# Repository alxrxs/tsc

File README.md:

---
# InkTime -- Smartwatch Open Source cu Display E-Paper
**TSC 2026 -- Andrei-Alexandru Bleortu, 334CA**

---

## Descriere proiect

InkTime este un smartwatch open source cu display e-paper, construit in jurul SoC-ului Nordic nRF52840. Schema electrica a fost furnizata de profesor; sarcina mea a fost sa o transpun in Fusion 360, sa realizez layout-ul PCB si sa-l integrez in carcasa data.

PCB-ul are dimensiunile 36x38mm, grosime 1mm, 4 straturi (TOP, GND, POWER, BOTTOM), cu toate componentele pe layer-ul TOP.

---

## Diagrama bloc

```
                          +--------------------------------------------+
                          |              nRF52840 (U1)                 |
                          |                                            |
  +--------------+  VBUS  |  USB/VBUS                                  |
  |  USB-C (J4)  |------->|                      P0.02 (SCK)  ---------+------------------+
  | KH-TYPE-C-16P|  D+/D- |  USB D+/D-           P0.03 (MOSI) ---------+--------------+   |
  +------+-------+<------>|                      P0.05 (CS)   ---------+----------+   |   |
         |                |  P0.06 (SDA)  ---------------------------- +--+       |   |   |
  +------v-------+        |  P0.07 (SCL)  ---------------------------- +--+ I2C   |   |   |
  |  USBLC6-2SC6Y|        |                      P0.15 (EPD_DC)  ------+--+       |   |SPI|
  |  ESD (D3)    |        |  P0.08 (IMU_INT1)                   P0.16 -+--+       |   |   |
  +------+-------+        |  P1.08 (IMU_INT2)                   P0.17 -+--+       |   |   |
         |                |  P0.11 (PMIC_INT)                          |          |   |   |
  +------v-------+  VREG  |  P0.10 (ALERT)        P1.01 (EPD PWR EN)-->|          |   |   |
  |  BQ25180YBGR |------->|  P0.12 (HAPTIC_EN)                         |          |   |   |
  |  Incarcator  |        |                                            |          |   |   |
  +------+-------+        |  P0.13 (SW1)                               |          |   |   |
         | VBAT           |  P0.14 (SW2)                               |          |   |   |
  +------v-------+        |  P1.02 (SW3)                               |          |   |   |
  |  Baterie     |        |              SWDIO/SWDCLK/SWO/RESET        |          |   |   |
  |  Li-Po       |        |  P0.00/P0.01 (XL1/XL2) <-- X2 32.768kHz    |          |   |   |
  +------+-------+        |  XC1/XC2  <--------------- X1 32MHz        |          |   |   |
         |                |                      ANT  --> Retea RF     |          |   |   |
  +------v-------+        +--------------------------------------------+          |   |   |
  | MAX17048G+T10|<------------------------------- I2C ---------------------------+   |   |
  | Fuel Gauge   |                                                                    |   |
  +--------------+        Magistrala I2C (SDA=P0.06, SCL=P0.07):                      |   |
                          +--------------+  +--------------+  +--------------+        |   |
                          | RT6160AWSC   |  |  BMA421 (IC3)|  | DRV2605YZFR  |        |   |
                          | Buck-Boost   |  |  IMU/Accel.  |  | Haptic (IC2) |        |   |
                          | -> 3V3 (IC9) |  |              |  | -> Motor     |        |   |
                          +--------------+  +--------------+  +--------------+        |   |
                                                                                      |   |
                          Magistrala SPI (SCK=P0.02, MOSI=P0.03):                     |   |
                          +-----------------------------------------------------------+   |
                          |  503480-2400 FPC (J2) -> Display E-Paper                      |
                          |  CS=P0.05, DC=P0.15, RST=P0.16, BUSY=P0.17  <-----------------+
                          +----------------------------------------------

                          Butoane: SW1(P0.13) SW2(P0.14) SW3(P1.02)
                          Debug:   TC2030-IDC (J1) -> SWD + RESET
                          Antena:  2450AT18B100E + retea de adaptare L-C
```

---

## Bill of Materials (BOM)

| Ref | Componenta | Valoare / MPN | Capsula | Cant | JLCPCB | Datasheet |
|-----|------------|---------------|---------|------|--------|-----------|
| U1 | MCU nRF52840 | NRF52840-QIAA-R | AQFN-74 (7x7mm) | 1 | [C190794](https://jlcpcb.com/partdetail/NordicSemiconductor-nRF52840QIAA/C190794) | [Datasheet](https://infocenter.nordicsemi.com/pdf/nRF52840_PS_v1.7.pdf) |
| IC1 | Incarcator baterie | BQ25180YBGR | DSBGA-8 (1.6x1.1mm) | 1 | [C3682423](https://jlcpcb.com/partdetail/C3682423) | [Datasheet](https://www.ti.com/lit/ds/symlink/bq25180.pdf) |
| IC9 | Regulator Buck-Boost DC-DC | RT6160AWSC | WLCSP-15 (2.3x1.4mm) | 1 | [C7065276](https://jlcpcb.com/partdetail/C7065276) | [Datasheet](https://www.richtek.com/assets/product_file/RT6160A/DS6160A-00.pdf) |
| IC3 | IMU / Accelerometru | BMA421 | LGA-12 (2x2mm) | 1 | [C5242966](https://jlcpcb.com/partdetail/BoschSensortec-BMA421/C5242966) | [Datasheet](https://files.pine64.org/doc/datasheet/pinetime/BST-BMA421-FL000.pdf) |
| IC2 | Driver motor haptic | DRV2605YZFR | DSBGA-9 | 1 | [C81079](https://jlcpcb.com/partdetail/C81079) | [Datasheet](https://www.ti.com/lit/ds/symlink/drv2605.pdf) |
| U2 | Fuel gauge Li-Po | MAX17048G+T10 | WLP-8 (0.9x1.8mm) | 1 | [C2682616](https://jlcpcb.com/partdetail/C2682616) | [Datasheet](https://www.analog.com/media/en/technical-documentation/data-sheets/max17048-max17049.pdf) |
| J4 | Conector USB-C | KH-TYPE-C-16P | SMD 16P | 1 | [C709357](https://jlcpcb.com/partdetail/C709357) | [Datasheet](https://datasheet.lcsc.com/lcsc/2108252330_Korean-Hroparts-Elec-TYPE-C-31-M-12_C165948.pdf) |
| J2 | Conector FPC (e-Paper) | 503480-2400 | SMD 24P, pas 0.5mm | 1 | [C122434](https://jlcpcb.com/partdetail/C122434) | [Datasheet](https://www.molex.com/content/dam/molex/molex-dot-com/products/automated/en-us/salesdrawingpdf/503/5034/503480-2400_sd.pdf) |
| J1 | Conector debug | TC2030-IDC | Tag-Connect 6P | 1 | N/A (footprint) | [Datasheet](https://www.tag-connect.com/wp-content/uploads/bsk-pdf-manager/TC2030-IDC-NL_Datasheet_8.pdf) |
| ANT1 | Antena chip 2.4GHz | 2450AT18B100E | SMD 1.6x0.8mm | 1 | [C2917717](https://jlcpcb.com/partdetail/C2917717) | [Datasheet](https://www.johansontechnology.com/datasheets/2450AT18B100E/2450AT18B100E.pdf) |
| D3 | Protectie ESD USB | USBLC6-2SC6Y | SOT-363 | 1 | [C2969755](https://jlcpcb.com/partdetail/C2969755) | [Datasheet](https://www.st.com/resource/en/datasheet/usblc6-2.pdf) |
| D2, D4, D5 | Dioda Schottky | MBR0530 | SOD-123 | 3 | [C232832](https://jlcpcb.com/partdetail/C232832) | [Datasheet](https://www.onsemi.com/pdf/datasheet/mbr0530t1-d.pdf) |
| Q1 | N-MOSFET (driver EPD) | SI1308EDL-T1-GE3 | SC-70-3 | 1 | [C469327](https://jlcpcb.com/partdetail/C469327) | [Datasheet](https://www.vishay.com/docs/66783/si1308edl.pdf) |
| Q2 | P-MOSFET (alimentare EPD) | DMG2305UX-7 | SOT-323 | 1 | [C150470](https://jlcpcb.com/partdetail/C150470) | [Datasheet](https://www.diodes.com/assets/Datasheets/DMG2305UX.pdf) |
| SW1, SW2, SW3 | Buton tactil | EVP-AKE31A | SMD | 3 | [C569760](https://jlcpcb.com/partdetail/C569760) | [Datasheet](https://industrial.panasonic.com/cdbs/www-data/pdf/ATV0000/ATV0000CE15.pdf) |
| X1 | Crystal HF | 32MHz | SMD 3225 | 1 | [C113671](https://jlcpcb.com/partdetail/C113671) | -- |
| X2 | Crystal LF (RTC) | 32.768kHz | SMD | 1 | [C145140](https://jlcpcb.com/partdetail/C145140) | -- |
| L7 | Inductor (DC-DC) | FTC252012SR47MBCA / 0.47uH | 0402 | 1 | [C5832368](https://jlcpcb.com/partdetail/C5832368) | [Datasheet](https://product.tdk.com/system/files/dam/doc/product/inductor/inductor/smd/catalog/inductor_commercial_power_mlp2016_en.pdf) |
| L1 | Inductor adaptare antena | 3.9nH | 0402 | 1 | -- | -- |
| L2 | Inductor decuplare RF | 10uH | 0402 | 1 | -- | -- |
| L3 | Inductor decuplare RF | 15nH | 0402 | 1 | -- | -- |
| L5 | Inductor (boost EPD) | 68uH | 0402 | 1 | -- | -- |
| C1, C2 | Condensator sarcina crystal HF | 12pF | 0201 | 2 | [C426109](https://jlcpcb.com/partdetail/C426109) | -- |
| C17, C18 | Condensator sarcina crystal LF | 12pF | 0201 | 2 | [C426109](https://jlcpcb.com/partdetail/C426109) | -- |
| C3, C4 | Condensator adaptare antena | 1pF | 0201 | 2 | [C185624](https://jlcpcb.com/partdetail/C185624) | -- |
| C8, C12, C7, C5 | Condensator decuplare | 100nF | 0201 | 4 | [C160831](https://jlcpcb.com/partdetail/C160831) | -- |
| C6, C14, C20, C21 | Condensator bulk | 4.7uF | 0402 | 4 | [C23687](https://jlcpcb.com/partdetail/C23687) | -- |
| C24, C39 | Condensator bulk (VREG) | 10uF | 0402 | 2 | [C105884](https://jlcpcb.com/partdetail/C105884) | -- |
| C25, C33 | Condensator iesire (3V3) | 22uF | 0402 | 2 | [C919306](https://jlcpcb.com/partdetail/C919306) | -- |
| C37, C38 | Condensator filtru PMIC | 1uF | 0402 | 2 | [C268023](https://jlcpcb.com/partdetail/C268023) | -- |
| R17, R18 | Rezistenta pull-up I2C | 3.3kohm | 0201 | 2 | [C274874](https://jlcpcb.com/partdetail/C274874) | -- |
| R5, R7, R8 | Rezistenta pull-up butoane | 10kohm | 0201 | 3 | [C106225](https://jlcpcb.com/partdetail/C106225) | -- |
| R9, R2_EP_DR, R_PWR_EPD | Pull-up / configurare | 10kohm | 0201 | 3 | [C106225](https://jlcpcb.com/partdetail/C106225) | -- |
| R1_USB, R2_USB | Rezistente CC USB-C | 5.1kohm | 0201 | 2 | [C274341](https://jlcpcb.com/partdetail/C274341) | -- |
| R1, R2, R4 | Jumper zero-ohm | 0ohm | 0201 | 3 | [C106227](https://jlcpcb.com/partdetail/C106227) | -- |
| R1_EP_DR | Rezistenta limitare curent EPD | 0.47ohm | 0201 | 1 | -- | -- |
| R_TYPE_SEL | Selectie tip display | 2.2ohm | 0201 | 1 | -- | -- |
| EPD_C1-C12 | Condensatoare HV EPD | 1uF/50V | 0402 | 9 | -- | -- |
| C29-C32 | Condensator debounce butoane | 1uF | 0402 | 4 | [C268023](https://jlcpcb.com/partdetail/C268023) | -- |

---

## Descriere hardware

### Componentele principale

**nRF52840 (U1)** -- MCU central. Cortex-M4F la 64MHz, 1MB flash, 256KB RAM, radio 2.4GHz integrat (BLE 5.0 + IEEE 802.15.4). Capsula AQFN-74, 7x7mm, 74 de pad-uri.

**BQ25180YBGR (IC1)** -- incarcator Li-Po single-cell de la Texas Instruments. Gestioneaza power path-ul USB-C, curentul de incarcare configurabil prin I2C (pana la 350mA), si semnalizeaza evenimentele de stare prin pinul INT (PMIC_INT -> P0.11). Adresa I2C: 0x6A.

**RT6160AWSC (IC9)** -- regulator buck-boost de la Richtek, WLCSP-15. Converteste tensiunea variabila a bateriei (3.0-4.2V) in 3.3V stabil pentru restul circuitului. Controlabil prin I2C. Adresa I2C: 0x75 (7-bit, conform datasheet sectiunea 16.23).

**BMA423 (IC3)** -- accelerometru triaxial Bosch, LGA-12 (2x2mm). Are numarator de pasi si detectie de gesturi integrate in hardware. Comunica prin I2C, adresa 0x18 (pinul CSB legat la 3V3, SDO legat la GND prin R1). Doua linii de intrerupere: INT1 -> P0.08, INT2 -> P1.08.

**DRV2605YZFR (IC2)** -- driver motor haptic de la Texas Instruments, DSBGA-9. Controleaza un motor ERM sau LRA, cu biblioteca de tipare de vibratie integrata. I2C, adresa 0x5A. Activat prin HAPTIC_EN (P0.12).

**MAX17048G+T10 (U2)** -- fuel gauge Li-Po de la Maxim/ADI, WLP-8. Estimeaza starea de incarcare a bateriei prin algoritmul ModelGauge (fara rezistenta de sunt). I2C, adresa 0x36. Semnalul !ALERT merge la P0.10.

---

### Arhitectura de alimentare

```
USB-C (5V VBUS)
     |
     v
BQ25180 (IC1) -- incarcare baterie + power path
     | SYS -> sina VREG
     v
RT6160 (IC9) -- buck-boost
     | VOUT = 3.3V -> sina 3V3
     v
nRF52840, BMA423, DRV2605, MAX17048
```

Alimentarea display-ului e-paper este separata: Q2 (P-MOSFET DMG2305UX-7) comuteaza sina EPD_3V3, controlat de P1.01. Tensiunile de gate driver (PREVGH/PREVGL, +/-20V) sunt generate de un circuit boost cu L5 (68uH), Q1 (N-MOSFET SI1308EDL) si trei diode Schottky MBR0530.

---

### Pini nRF52840 utilizati

| GPIO | Functie | Conectat la |
|------|---------|-------------|
| P0.00 / XL1 | Crystal LF XL1 | X2 (32.768kHz) |
| P0.01 / XL2 | Crystal LF XL2 | X2 (32.768kHz) |
| P0.02 | SPI SCK | J2 pin 13 (display) |
| P0.03 | SPI MOSI | J2 pin 14 (display) |
| P0.05 | EPD CS | J2 pin 12 |
| P0.06 | I2C SDA | IC1, IC9, IC3, U2, IC2 |
| P0.07 | I2C SCL | IC1, IC9, IC3, U2, IC2 |
| P0.08 | IMU INT1 | IC3 (BMA423) |
| P0.10 / NFC2 | ALERT (fuel gauge) | U2 (MAX17048) |
| P0.11 | PMIC_INT | IC1 (BQ25180) |
| P0.12 | HAPTIC_EN | IC2 (DRV2605) |
| P0.13 | SW1 | Buton + pull-up 10kohm |
| P0.14 | SW2 | Buton + pull-up 10kohm |
| P0.15 | EPD DC | J2 pin 11 |
| P0.16 | EPD RST | J2 pin 10 |
| P0.17 | EPD BUSY | J2 pin 9 |
| P0.18 / RESET | RESET | TC2030 J1, TP_RESET |
| P1.00 | SWO | TC2030 J1, TP_SWO |
| P1.01 | EPD power enable | Gate Q2 |
| P1.02 | SW3 | Buton + pull-up 10kohm |
| P1.08 | IMU INT2 | IC3 (BMA423) |
| SWDIO | SWD Data | TC2030 J1, TP_SWDIO |
| SWDCLK | SWD Clock | TC2030 J1, TP_SWDCLK |
| VBUS | Detectare VBUS | BQ25180 IN + J4 |
| D+ / D- | USB Full-Speed | USBLC6-2SC6Y (D3) |
| XC1, XC2 | Crystal HF | X1 (32MHz) |

Pinii P0.04, P0.09, P0.19-P0.31, P1.03-P1.07, P1.09-P1.15 nu sunt utilizati in schema.

---

### Interfete de comunicatie

**I2C** (SDA=P0.06, SCL=P0.07) -- magistrala partajata cu 5 dispozitive:
- BQ25180 (0x6A) -- incarcator
- RT6160 (0x75) -- regulator DC-DC
- BMA423 (0x18) -- IMU
- MAX17048 (0x36) -- fuel gauge
- DRV2605 (0x5A) -- driver haptic

Pull-up-uri de 3.3kohm (R17, R18) pe ambele linii. R4 si R2 sunt rezistente de 0ohm care conecteaza IC9 (RT6160) la magistrala -- pot fi inlaturate pentru izolare la nevoie.

**SPI** (SCK=P0.02, MOSI=P0.03, CS=P0.05) -- exclusiv pentru display-ul e-paper prin conectorul FPC J2 (Molex 503480-2400, 24 pini, pas 0.5mm). Semnale suplimentare: DC (P0.15), RST (P0.16), BUSY (P0.17).

**USB Full-Speed** -- D+/D- merg prin USBLC6-2SC6Y (D3) pentru protectie ESD, apoi la pinii dedicati ai nRF52840. Rezistentele CC de 5.1kohm (R1_USB, R2_USB) identifica dispozitivul ca UFP pe USB-C.

**SWD** -- SWDIO, SWDCLK, SWO (P1.00), RESET (P0.18) disponibili prin conectorul Tag-Connect TC2030-IDC (J1) si pad-urile de test corespunzatoare.

---

### Ceas si RF

**Cristale:** X1 (32MHz) pe pinii XC1/XC2 -- necesar pentru radio BLE. X2 (32.768kHz) pe P0.00/P0.01 (XL1/XL2) -- pentru RTC. Condensatori de sarcina de 12pF pe ambele cristale.

**Antena:** 2450AT18B100E (Johanson Technology), chip antenna SMD 1.6x0.8mm. Conectata prin retea de adaptare Pi: L1 (3.9nH) serie si C3/C4 (1pF) shunt. C22 montat N.C. (rezervat pentru acordaj). Antena este plasata la marginea PCB-ului, cu decupaj in placa sub ea -- fara cupru si fara trasee in acea zona.

---

### Butoane

Trei butoane tactile Panasonic EVP-AKE31A, active-low, cu pull-up de 10kohm la 3V3 si condensator de debounce de 1uF pe fiecare linie.

| Buton | GPIO | Pull-up | Debounce |
|-------|------|---------|----------|
| SW1 | P0.13 | R5 | C30 |
| SW2 | P0.14 | R8 | C31 |
| SW3 | P1.02 | R7 | C29 |

---

### Debug

TC2030-IDC (J1) -- footprint Tag-Connect, fara conector fizic pe placa. Pinout:

| Pin | Semnal |
|-----|--------|
| 1 | 3V3 |
| 2 | SWDIO |
| 3 | GND |
| 4 | SWDCLK |
| 5 | GND |
| 6 | RESET |

Pad-uri de test disponibile in silkscreen: TP_SWDIO, TP_SWDCLK, TP_SWO, TP_RESET, TP_3.3V, TP_GND, TP_VBAT, TP_BAT_GND, TP_3V3, TP_VREG, TP_SCL, TP_SDA, TP_OP, TP_ON.

---

## Estimari consum

Calcule estimative bazate pe datasheeturile componentelor.

| Mod | Contribuitori | Curent estimat |
|-----|---------------|----------------|
| Deep sleep (doar RTC) | nRF52840 system-on: ~2.6uA, BMA423 low-power: ~3.5uA, MAX17048: ~3uA, RT6160 quiescent: ~60uA, DRV2605 standby: ~40uA | **~110uA** |
| BLE advertising (1s interval) | nRF52840 medie advertising: ~0.5mA + ~110uA sistem | **~0.6mA** |
| Activ (BLE conectat + refresh display) | nRF52840: ~4mA, varf refresh: ~26mA (cateva secunde), IMU: ~150uA | **~5-30mA** |
| Incarcare USB | BQ25180 la 200mA | **~200mA** |

Cu o baterie de 400mAh si un tipar de utilizare de ~5 minute activ + 55 minute standby pe ora, curentul mediu iese in jur de 0.5-0.6mA, ceea ce teoretic da cateva saptamani de autonomie. In practica, cu stack-ul BLE si refresh-uri regulate de display, realitatea va fi probabil undeva la 5-7 zile.

---

## Note PCB

Schema electrica a fost furnizata de dl. Tudose. Munca mea a constat in transpunerea ei in Fusion 360 si realizarea layout-ului PCB conform specificatiilor primite.

**Constrangeri respectate:**
- PCB 4 straturi: TOP (componente + rutare), GND (plan de masa dedicat), POWER (plan de alimentare), BOTTOM (rutare)
- Toate componentele plasate pe layer-ul TOP
- Trasee de putere (3V3, VBUS, VREG) cu latime 0.3mm; semnale de date minimum 0.15mm
- Condensatoarele de decuplare de 100nF plasate cat mai aproape de pinii de alimentare ai IC-urilor
- Fara cupru si fara trasee sub antena; decupaj PCB inclus sub 2450AT18B100E
- Fara unghiuri de 90deg in trasee

**Observatie privind BMA421 vs BMA423:** in schema deviceset-ul este BMA423, dar valoarea componentei scrie BMA421. Cele doua sunt pin-compatibile (acelasi footprint LGA-12, 2x2mm), deci nu afecteaza PCB-ul.

---

## Structura repository-ului

```
+-- Hardware/
|   +-- Schematic.sch          -- Schema electrica (Fusion 360 / Eagle)
|   +-- Board.brd              -- Layout PCB (Fusion 360 / Eagle)
|   +-- Schematic.pdf          -- Printout schema
+-- Manufacturing/
|   +-- gerbers.zip            -- Fisiere Gerber pentru fabricare
|   +-- InkTime.bom            -- Bill of Materials (CSV)
|   +-- InkTime.cpl            -- Pick and Place (CSV)
+-- Mechanical/
|   +-- InkTime_complete.step  -- Vedere 3D explodata (STEP)
|   +-- InkTime_complete.f3d   -- Asamblare Fusion 360
+-- Images/
|   +-- *.png                  -- Randari PCB si 3D
+-- LICENSE                    -- Apache 2.0
+-- README.md                  -- Acest fisier
```

---

## Licenta

GNU Affero General Public License. Vezi [LICENSE](LICENSE).

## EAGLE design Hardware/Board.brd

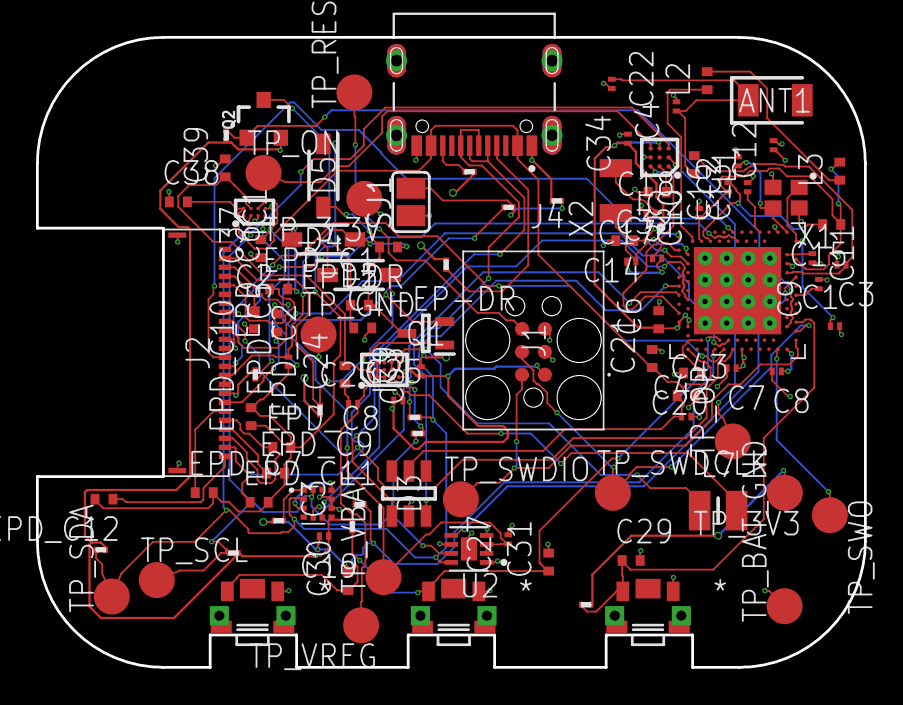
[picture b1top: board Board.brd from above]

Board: 4 copper layers, 46.0 x 35.0 mm, 105 parts (0 on the bottom side), 73 nets.

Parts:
ANT1: 2450AT18B100E; 2450AT18B100E_ANTC3216X140N
C1, C2, C17, C18: 12pF; NORDIC_NRF_3_RESC0201_L
C1-EP-DR, C24, C39: 10uF; NORDIC_NRF_3_RESC0402_L
C2-EP-DR: 4.7uF/25V; NORDIC_NRF_3_RESC0402_L
C3, C4: 1pF; NORDIC_NRF_3_RESC0201_L
C5, C7, C8, C12, C19: 100nF; NORDIC_NRF_3_RESC0201_L
C6, C14, C20, C21, C43: 4.7uF; NORDIC_NRF_3_RESC0402_L
C9: 820pF; NORDIC_NRF_3_RESC0201_L
C10, C13, C22: N.C.; NORDIC_NRF_3_RESC0201_L
C11: 100pF; NORDIC_NRF_3_RESC0201_L
C15: 1.0uF; NORDIC_NRF_3_RESC0402_L
C16: 47nF; NORDIC_NRF_3_RESC0201_L
C23, C27, C34, C42: 0.1uF; NORDIC_NRF_3_RESC0201_L
C25, C33: 22uF; NORDIC_NRF_3_RESC0201_L
C29, C30, C31, C32, C37, C38: 1uF; NORDIC_NRF_3_RESC0402_L
D2, D4, D5: MBR0530; ESP32_C6_LIBRARY_5_SOD3716X135N
D3: USBLC6-2SC6Y; ESP32_C6_LIBRARY_3_SOT95P280X145-6N
EPD_C1, EPD_C2, EPD_C6, EPD_C7, EPD_C8, EPD_C9, EPD_C10, EPD_C11, EPD_C12: 1uF/50V; NORDIC_NRF_3_RESC0402_L
EPD_C5: 0.1uF/50V; NORDIC_NRF_3_RESC0201_L
IC1: BQ25180YBGR; BQ25180YBGR_BGA8C40P2X4_100X155X50
IC2: DRV2605YZFR; DRV2605YZFR_BGA9C50P3X3_144X144X62
IC3: BMA421; BMA423_BMA423
IC9: RT6160AWSC; RT6160AWSC_BGA15C40P3X5_140X230X60
J1: TC2030-IDC; TC2030-IDC_TC2030IDC
J2: 503480-2400; 503480-2400_5034802400
J4: KH-TYPE-C-16P; KH-TYPE-C-16P_KINGHELM_KH-TYPE-C-16P
L1: 3.9nH; NORDIC_NRF_2_RESC0402_L
L2: 10uH; NORDIC_NRF_2_RESC0402_L
L3: 15nH; NORDIC_NRF_2_RESC0402_L
L5: 68uH; NORDIC_NRF_2_RESC0402_L
L7: FTC252012SR47MBCA; MLP2016SR47MT0S1_INDC2016X100N
Q1: SI1308EDL-T1-GE3; ESP32_C6_LIBRARY_6_SOT65P210X110-3N
Q2: 20V/4.2A/52mΩ/1.4W; ESP32_C6_LIBRARY_4_ESP32_C6_LIBRARY_4_ESP32_C6_LIBRARY_4_ES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
R1, R2, R4: 0; CPF0201D7K68C1_0201
R1_EP_DR: 0.47; CPF0201D7K68C1_0201
R1_USB, R2_USB: 5K1; CPF0201D7K68C1_0201
R2_EP_DR, R5, R7, R8, R9: 10K; CPF0201D7K68C1_0201
R17, R18: 3K3; CPF0201D7K68C1_0201
R_PWR_EPD: 10K; CPF0201D7K68C1_0201
R_TYPE_SEL: 2.2; CPF0201D7K68C1_0201
SJ1: ESP32_C6_LIBRARY_7_JUMPER_SJ
SW1, SW2, SW3: 2025-10-22_07-23-44_LIBRARY_EVP-AKE31ASW_EVP-AKE3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; 2025-10-22_07-23-44_LIBRARY_SW_EVP-AKE31A_PAN
TP_3.3V, TP_3V3: HECTOR_WATCH_1_TPTP20R; HECTOR_WATCH_1_TP20R
TP_BAT_GND: HECTOR_WATCH_1_TPTP20R; HECTOR_WATCH_1_TP20R
TP_GND: HECTOR_WATCH_1_TPTP20R; HECTOR_WATCH_1_TP20R
TP_ON: HECTOR_WATCH_1_TPTP20R; HECTOR_WATCH_1_TP20R
TP_OP: HECTOR_WATCH_1_TPTP20R; HECTOR_WATCH_1_TP20R
TP_RESET: HECTOR_WATCH_1_TPTP20R; HECTOR_WATCH_1_TP20R
TP_SCL: HECTOR_WATCH_1_TPTP20R; HECTOR_WATCH_1_TP20R
TP_SDA: HECTOR_WATCH_1_TPTP20R; HECTOR_WATCH_1_TP20R
TP_SWDCLK: HECTOR_WATCH_1_TPTP20R; HECTOR_WATCH_1_TP20R
TP_SWDIO: HECTOR_WATCH_1_TPTP20R; HECTOR_WATCH_1_TP20R
TP_SWO: HECTOR_WATCH_1_TPTP20R; HECTOR_WATCH_1_TP20R
TP_VBAT: HECTOR_WATCH_1_TPTP20R; HECTOR_WATCH_1_TP20R
TP_VREG: HECTOR_WATCH_1_TPTP20R; HECTOR_WATCH_1_TP20R
U1: NRF52840 _QF; NORDIC_NRF_4_AQFN50P700X700X85_HS-74N
U2: MAX17048G+T10; ESP32_C6_LIBRARY_SON50P200X200X80-9N
X1: 32MHz; NORDIC_NRF_BT-XTAL_2016_N
X2: 32.768kHz; NORDIC_NRF_1_XTAL_3215_N

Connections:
3V3: C6.1, C7.1, C8.1, C12.1, C14.1, C19.1, C25.1, C33.1, C34.1, IC2.C2, IC3.3, IC3.7, IC3.10, IC9.E2, IC9.E3, J1.1, Q2.2, R5.2, R7.2, R8.2, R17.1, R18.1, R_PWR_EPD.2, TP_3.3V.TP, TP_3V3.TP, U1.P$A22, U1.P$AD14, U1.P$AD23, U1.P$B1, U1.P$W1, U1.P$Y2
ALERT: U1.P$J24, U2.5
D+: D3.4, U1.P$AD6
D-: D3.6, U1.P$AD4
DN: D3.1, J4.A7, J4.B7
DP: D3.3, J4.A6, J4.B6
EPD_3V3: C1-EP-DR.1, EPD_C5.2, J2.15, J2.16, L5.1, Q2.3
EPD_BUSY: J2.9, U1.P$AD12
EPD_CS: J2.12, U1.P$K2
EPD_DC: J2.11, U1.P$AD10
EPD_RST: J2.10, U1.P$AC11
GDR: J2.2, Q1.1, R2_EP_DR.2
GND: C1.2, C1-EP-DR.2, C2.2, C3.2, C4.2, C5.2, C6.2, C7.2, C8.2, C9.2, C10.2, C11.2, C12.2, C13.2, C14.2, C17.1, C18.1, C19.2, C20.2, C21.2, C22.2, C25.2, C27.2, C29.2, C30.2, C31.2, C32.2, C33.2, C34.2, C37.1, C38.1, C39.2, C42.2, C43.2, D3.2, D4.1, EPD_C1.2, EPD_C2.2, IC1.D2, IC2.B1, IC2.B3, IC3.8, IC3.9, IC9.C3, J1.3, J1.5, J2.8, J2.17, J2.MP1, J2.MP2, J4.A1_B12, J4.A12_B1, J4.SH1, J4.SH2, J4.SH3, J4.SH4, R1.1, R1_USB.1, R2_EP_DR.1, R2_USB.2, R9.1, R_TYPE_SEL.1, SJ1.1, SW1.1, SW2.1, SW3.1, TP_BAT_GND.TP, TP_GND.TP, U1.P$74, U1.P$75, U1.P$76, U1.P$77, U1.P$78, U1.P$79, U1.P$80, U1.P$81, U1.P$82, U1.P$83, U1.P$84, U1.P$85, U1.P$86, U1.P$87, U1.P$88, U1.P$89, U1.P$90, U1.P$F23, U2.1, U2.4, U2.6, U2.9, X1.2, X1.4
HAPTIC_EN: IC2.A1, U1.P$U1
IMU_INT1: IC3.5, U1.P$N1
IMU_INT2: IC3.6, U1.P$P2
LX1: IC9.B1, IC9.B2, IC9.B3, IC9.C1, IC9.C2, L7.1
LX2: IC9.D2, IC9.D3, L7.2
MOSI: J2.14, U1.P$B13
unnamed: ANT1.1, C4.1, C22.1, L1.2
unnamed: C9.1, U1.P$N24
unnamed: C23.1, C24.1
unnamed: C3.1, L1.1, U1.P$H23
unnamed: IC9.D1, R4.2
unnamed: IC1.D1, R9.2
unnamed: IC9.E1, R2.2
unnamed: C20.1, U1.P$AC5
unnamed: C5.1, U1.P$C1
unnamed: C32.1, IC2.A2
unnamed: C2-EP-DR.2, D5.2, L5.2, Q1.3
unnamed: C2-EP-DR.1, D2.1, D4.2
unnamed: IC3.1, R1.2
unnamed: R1_EP_DR.1, R_TYPE_SEL.2, SJ1.2
unnamed: C18.2, U1.P$F2, X2.2
unnamed: C17.2, U1.P$D2, X2.1
unnamed: C10.1, C15.1, C16.1, L3.2, U1.P$B5, U1.P$E24
unnamed: L2.1, U1.P$B3
unnamed: C15.2, C16.2, U1.P$B7
unnamed: L2.2, L3.1
unnamed: C11.1, U1.P$D23
unnamed: C2.1, U1.P$A23, X1.3
unnamed: C1.1, U1.P$B24, X1.1
unnamed: C13.1, U1.P$A18
unnamed: EPD_C12.1, J2.24
unnamed: EPD_C6.1, J2.18
unnamed: EPD_C7.1, J2.19
unnamed: EPD_C8.1, J2.20
unnamed: EPD_C9.1, J2.21
unnamed: EPD_C10.1, J2.22
unnamed: J4.A5, R1_USB.2
unnamed: EPD_C1.1, J2.5
unnamed: EPD_C2.1, J2.4
unnamed: J4.B5, R2_USB.1
OUT+: IC2.A3, TP_OP.TP
OUT-: IC2.C3, TP_ON.TP
P0.13: C30.1, R5.1, SW1.2, U1.P$AD8
P0.14: C31.1, R8.1, SW2.2, U1.P$AC9
P1.01: Q2.1, R_PWR_EPD.1, U1.P$Y23
P1.02: C29.1, R7.1, SW3.2, U1.P$W24
PMIC_INT: IC1.A1, U1.P$T2
PREVGH: D5.1, EPD_C5.1, EPD_C6.2, EPD_C7.2, EPD_C8.2, EPD_C9.2, EPD_C10.2, EPD_C11.2, EPD_C12.2
PREVGL: D2.2, EPD_C11.1, J2.23
RESE: J2.3, Q1.2, R1_EP_DR.2
RESET: J1.6, TP_RESET.TP, U1.P$AC13
SCK: J2.13, U1.P$A12
SCL: IC1.B1, IC2.C1, IC3.12, R4.1, R17.2, TP_SCL.TP, U1.P$M2, U2.7
SDA: IC1.C1, IC2.B2, IC3.2, R2.1, R18.2, TP_SDA.TP, U1.P$L1, U2.8
SWDCLK: J1.4, TP_SWDCLK.TP, U1.P$AA24
SWDIO: J1.2, TP_SWDIO.TP, U1.P$AC24
SWO: TP_SWO.TP, U1.P$AD22
VBAT: C27.1, C37.2, IC1.C2, TP_VBAT.TP, U2.2, U2.3
VBUS: C21.1, C38.2, C42.1, C43.1, D3.5, IC1.A2, J4.A4_B9, J4.A9_B4, U1.P$AD2
VREG: C23.2, C24.2, C39.1, IC1.B2, IC9.A1, IC9.A2, IC9.A3, TP_VREG.TP

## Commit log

2026-04-10 Correct License
2026-04-17 Add initial PCB, bill of materials and README
2026-04-19 Correct electrical schematic as per feedback contents
2026-04-19 Update README.md with changed part number
2026-04-19 Change switch model value
2026-04-22 Add official submission
2026-04-27 Add file via upload

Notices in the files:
README.md:
GNU Affero General Public License. Vezi [LICENSE](LICENSE).
parts and their libraries:
COPYRIGHT: Copyright (C) 2025 Ultra Librarian. All rights reserved.
